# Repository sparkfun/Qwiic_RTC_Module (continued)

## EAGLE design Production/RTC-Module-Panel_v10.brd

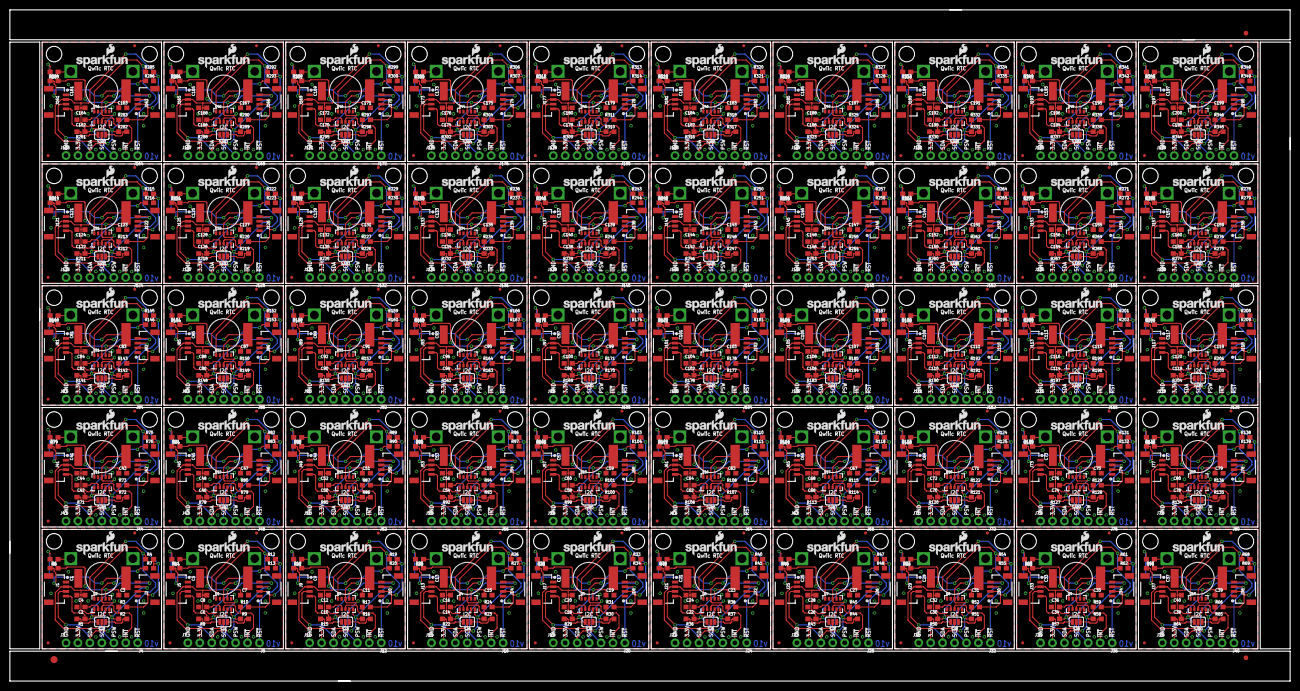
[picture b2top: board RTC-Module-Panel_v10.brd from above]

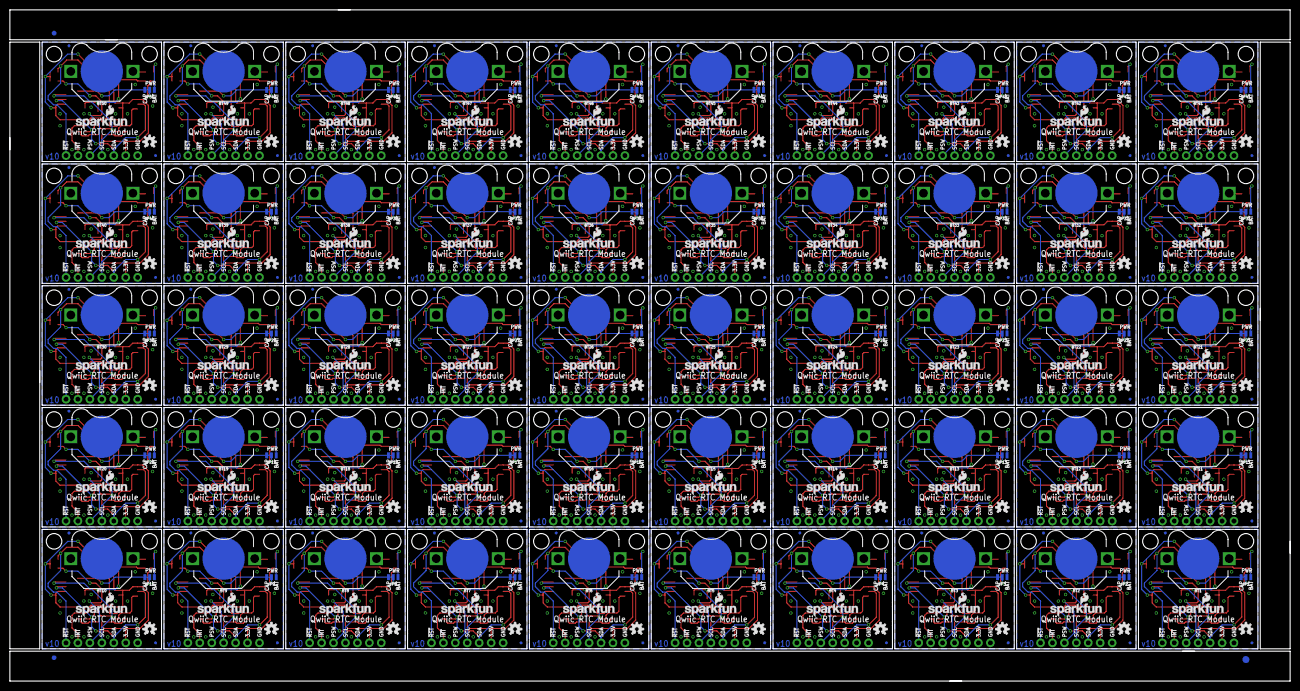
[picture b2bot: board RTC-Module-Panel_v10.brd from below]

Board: 2 copper layers, 272.3 x 142.7 mm, 1406 parts (303 on the bottom side), 750 nets.

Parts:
BT1, BT2, BT3, BT4, BT5, BT6, BT7, BT8, BT9, BT10, BT11, BT12, BT13, BT14, BT15, BT16, BT17, BT18, BT19, BT20, BT21, BT22, BT23, BT24, BT25, BT26, BT27, BT28, BT29, BT30, BT31, BT32, BT33, BT34, BT35, BT36, BT37, BT38, BT39, BT40, BT41, BT42, BT43, BT44, BT45, BT46, BT47, BT48, BT49, BT50: BATTCON_12MM_PTH
C1, C5, C9, C13, C17, C21, C25, C29, C33, C37, C41, C45, C49, C53, C57, C61, C65, C69, C73, C77, C81, C85, C89, C93, C97, C101, C105, C109, C113, C117, C121, C125, C129, C133, C137, C141, C145, C149, C153, C157, C161, C165, C169, C173, C177, C181, C185, C189, C193, C197: .22F-SUPERCAP; DSK-RADIAL-6.8MM
C2, C6, C10, C14, C18, C22, C26, C30, C34, C38, C42, C46, C50, C54, C58, C62, C66, C70, C74, C78, C82, C86, C90, C94, C98, C102, C106, C110, C114, C118, C122, C126, C130, C134, C138, C142, C146, C150, C154, C158, C162, C166, C170, C174, C178, C182, C186, C190, C194, C198: 47pF; 0603
C3, C4, C7, C8, C11, C12, C15, C16, C19, C20, C23, C24, C27, C28, C31, C32, C35, C36, C39, C40, C43, C44, C47, C48, C51, C52, C55, C56, C59, C60, C63, C64, C67, C68, C71, C72, C75, C76, C79, C80, C83, C84, C87, C88, C91, C92, C95, C96, C99, C100, C103, C104, C107, C108, C111, C112, C115, C116, C119, C120, C123, C124, C127, C128, C131, C132, C135, C136, C139, C140, C143, C144, C147, C148, C151, C152, C155, C156, C159, C160, C163, C164, C167, C168, C171, C172, C175, C176, C179, C180, C183, C184, C187, C188, C191, C192, C195, C196, C199, C200: 10nF; 0603
E$1, E$2: FIDUCIAL-1.5X3
E$3, E$4, E$6, E$7: FIDUCIAL-1X2
FD1, FD2, FD3, FD4, FD5, FD6, FD7, FD8, FD9, FD10, FD11, FD12, FD13, FD14, FD15, FD16, FD17, FD18, FD19, FD20, FD21, FD22, FD23, FD24, FD25, FD26, FD27, FD28, FD29, FD30, FD31, FD32, FD33, FD34, FD35, FD36, FD37, FD38, FD39, FD40, FD41, FD42, FD43, FD44, FD45, FD46, FD47, FD48, FD49, FD50, FD51, FD52, FD53, FD54, FD55, FD56, FD57, FD58, FD59, FD60, FD61, FD62, FD63, FD64, FD65, FD66, FD67, FD68, FD69, FD70, FD71, FD72, FD73, FD74, FD75, FD76, FD77, FD78, FD79, FD80, FD81, FD82, FD83, FD84, FD85, FD86, FD87, FD88, FD89, FD90, FD91, FD92, FD93, FD94, FD95, FD96, FD97, FD98, FD99, FD100, FD101, FD102, FD103, FD104, FD105, FD106, FD107, FD108, FD109, FD110, FD111, FD112, FD113, FD114, FD115, FD116, FD117, FD118, FD119, FD120, FD121, FD122, FD123, FD124, FD125, FD126, FD127, FD128, FD129, FD130, FD131, FD132, FD133, FD134, FD135, FD136, FD137, FD138, FD139, FD140, FD141, FD142, FD143, FD144, FD145, FD146, FD147, FD148, FD149, FD150, FD151, FD152, FD153, FD154, FD155, FD156, FD157, FD158, FD159, FD160, FD161, FD162, FD163, FD164, FD165, FD166, FD167, FD168, FD169, FD170, FD171, FD172, FD173, FD174, FD175, FD176, FD177, FD178, FD179, FD180, FD181, FD182, FD183, FD184, FD185, FD186, FD187, FD188, FD189, FD190, FD191, FD192, FD193, FD194, FD195, FD196, FD197, FD198, FD199, FD200: FIDUCIALUFIDUCIAL; FIDUCIAL-MICRO
J1, J2, J5, J6, J9, J10, J13, J14, J17, J18, J21, J22, J25, J26, J29, J30, J33, J34, J37, J38, J41, J42, J45, J46, J49, J50, J53, J54, J57, J58, J61, J62, J65, J66, J69, J70, J73, J74, J77, J78, J81, J82, J85, J86, J89, J90, J93, J94, J97, J98, J101, J102, J105, J106, J109, J110, J113, J114, J117, J118, J121, J122, J125, J126, J129, J130, J133, J134, J137, J138, J141, J142, J145, J146, J149, J150, J153, J154, J157, J158, J161, J162, J165, J166, J169, J170, J173, J174, J177, J178, J181, J182, J185, J186, J189, J190, J193, J194, J197, J198: SMD; 1X04_1MM_RA
J3, J7, J11, J15, J19, J23, J27, J31, J35, J39, J43, J47, J51, J55, J59, J63, J67, J71, J75, J79, J83, J87, J91, J95, J99, J103, J107, J111, J115, J119, J123, J127, J131, J135, J139, J143, J147, J151, J155, J159, J163, J167, J171, J175, J179, J183, J187, J191, J195, J199: PTH; 1X04_NO_SILK
J4, J8, J12, J16, J20, J24, J28, J32, J36, J40, J44, J48, J52, J56, J60, J64, J68, J72, J76, J80, J84, J88, J92, J96, J100, J104, J108, J112, J116, J120, J124, J128, J132, J136, J140, J144, J148, J152, J156, J160, J164, J168, J172, J176, J180, J184, J188, J192, J196, J200: 1X03_NO_SILK
JP1, JP2, JP3, JP4, JP5, JP6, JP7, JP8, JP9, JP10, JP11, JP12, JP13, JP14, JP15, JP16, JP17, JP18, JP19, JP20, JP21, JP22, JP23, JP24, JP25, JP26, JP27, JP28, JP29, JP30, JP31, JP32, JP33, JP34, JP35, JP36, JP37, JP38, JP39, JP40, JP41, JP42, JP43, JP44, JP45, JP46, JP47, JP48, JP49, JP50: JUMPER-SMT_3_1-NC_TRACE_NO-SILK; SMT-JUMPER_3_1-NC_TRACE_NO-SILK
LOGO1, LOGO4, LOGO7, LOGO10, LOGO13, LOGO16, LOGO19, LOGO22, LOGO25, LOGO28, LOGO31, LOGO34, LOGO37, LOGO40, LOGO43, LOGO46, LOGO49, LOGO52, LOGO55, LOGO58, LOGO61, LOGO64, LOGO67, LOGO70, LOGO73, LOGO76, LOGO79, LOGO82, LOGO85, LOGO88, LOGO91, LOGO94, LOGO97, LOGO100, LOGO103, LOGO106, LOGO109, LOGO112, LOGO115, LOGO118, LOGO121, LOGO124, LOGO127, LOGO130, LOGO133, LOGO136, LOGO139, LOGO142, LOGO145, LOGO148: OSHW-LOGOS; OSHW-LOGO-S
LOGO2, LOGO3, LOGO5, LOGO6, LOGO8, LOGO9, LOGO11, LOGO12, LOGO14, LOGO15, LOGO17, LOGO18, LOGO20, LOGO21, LOGO23, LOGO24, LOGO26, LOGO27, LOGO29, LOGO30, LOGO32, LOGO33, LOGO35, LOGO36, LOGO38, LOGO39, LOGO41, LOGO42, LOGO44, LOGO45, LOGO47, LOGO48, LOGO50, LOGO51, LOGO53, LOGO54, LOGO56, LOGO57, LOGO59, LOGO60, LOGO62, LOGO63, LOGO65, LOGO66, LOGO68, LOGO69, LOGO71, LOGO72, LOGO74, LOGO75, LOGO77, LOGO78, LOGO80, LOGO81, LOGO83, LOGO84, LOGO86, LOGO87, LOGO89, LOGO90, LOGO92, LOGO93, LOGO95, LOGO96, LOGO98, LOGO99, LOGO101, LOGO102, LOGO104, LOGO105, LOGO107, LOGO108, LOGO110, LOGO111, LOGO113, LOGO114, LOGO116, LOGO117, LOGO119, LOGO120, LOGO122, LOGO123, LOGO125, LOGO126, LOGO128, LOGO129, LOGO131, LOGO132, LOGO134, LOGO135, LOGO137, LOGO138, LOGO140, LOGO141, LOGO143, LOGO144, LOGO146, LOGO147, LOGO149, LOGO150: SFE_LOGO_NAME_FLAME.1_INCH; SFE_LOGO_NAME_FLAME_.1
R1, R2, R8, R9, R15, R16, R22, R23, R29, R30, R36, R37, R43, R44, R50, R51, R57, R58, R64, R65, R71, R72, R78, R79, R85, R86, R92, R93, R99, R100, R106, R107, R113, R114, R120, R121, R127, R128, R134, R135, R141, R142, R148, R149, R155, R156, R162, R163, R169, R170, R176, R177, R183, R184, R190, R191, R197, R198, R204, R205, R211, R212, R218, R219, R225, R226, R232, R233, R239, R240, R246, R247, R253, R254, R260, R261, R267, R268, R274, R275, R281, R282, R288, R289, R295, R296, R302, R303, R309, R310, R316, R317, R323, R324, R330, R331, R337, R338, R344, R345: 2.2k; 0603
R3, R4, R7, R10, R12, R13, R17, R19, R20, R24, R26, R27, R31, R33, R34, R38, R40, R41, R45, R47, R48, R52, R54, R55, R59, R61, R62, R66, R68, R69, R73, R75, R76, R80, R82, R83, R87, R89, R90, R94, R96, R97, R101, R103, R104, R108, R110, R111, R115, R117, R118, R122, R124, R125, R129, R131, R132, R136, R138, R139, R143, R145, R146, R150, R152, R153, R157, R159, R160, R164, R166, R167, R171, R173, R174, R178, R180, R181, R185, R187, R188, R192, R194, R195, R199, R201, R202, R206, R208, R209, R213, R215, R216, R220, R222, R223, R227, R229, R230, R234, R236, R237, R241, R243, R244, R248, R250, R251, R255, R257, R258, R262, R264, R265, R269, R271, R272, R276, R278, R279, R283, R285, R286, R290, R292, R293, R297, R299, R300, R304, R306, R307, R311, R313, R314, R318, R320, R321, R325, R327, R328, R332, R334, R335, R339, R341, R342, R346, R348, R349: 10k; 0603
R5, R14, R21, R28, R35, R42, R49, R56, R63, R70, R77, R84, R91, R98, R105, R112, R119, R126, R133, R140, R147, R154, R161, R168, R175, R182, R189, R196, R203, R210, R217, R224, R231, R238, R245, R252, R259, R266, R273, R280, R287, R294, R301, R308, R315, R322, R329, R336, R343, R350: 470; 0603
R6, R11, R18, R25, R32, R39, R46, R53, R60, R67, R74, R81, R88, R95, R102, R109, R116, R123, R130, R137, R144, R151, R158, R165, R172, R179, R186, R193, R200, R207, R214, R221, R228, R235, R242, R249, R256, R263, R270, R277, R284, R291, R298, R305, R312, R319, R326, R333, R340, R347: 1k; 0603
SJ1, SJ2, SJ3, SJ4, SJ5, SJ6, SJ7, SJ8, SJ9, SJ10, SJ11, SJ12, SJ13, SJ14, SJ15, SJ16, SJ17, SJ18, SJ19, SJ20, SJ21, SJ22, SJ23, SJ24, SJ25, SJ26, SJ27, SJ28, SJ29, SJ30, SJ31, SJ32, SJ33, SJ34, SJ35, SJ36, SJ37, SJ38, SJ39, SJ40, SJ41, SJ42, SJ43, SJ44, SJ45, SJ46, SJ47, SJ48, SJ49, SJ50: JUMPER-SMT_3_2-NC_PASTE_SILK; SMT-JUMPER_3_2-NC_PASTE_SILK
U1, U2, U3, U4, U5, U6, U7, U8, U9, U10, U11, U12, U13, U14, U15, U16, U17, U18, U19, U20, U21, U22, U23, U24, U25, U26, U27, U28, U29, U30, U31, U32, U33, U34, U35, U36, U37, U38, U39, U40, U41, U42, U43, U44, U45, U46, U47, U48, U49, U50: RV-1805
U$1, U$2, U$3, U$4, U$5, U$6, U$7, U$8, U$9, U$10, U$11, U$12, U$13, U$14, U$15, U$16, U$17, U$18, U$19, U$20, U$21, U$22, U$23, U$24, U$25, U$26, U$27, U$28, U$29, U$30, U$31, U$32, U$33, U$34, U$35, U$36, U$37, U$38, U$39, U$40, U$41, U$42, U$43, U$44, U$45, U$46, U$47, U$48, U$49, U$50, U$51, U$52, U$53, U$54, U$55, U$56, U$57, U$58, U$59, U$60, U$61, U$62, U$63, U$64, U$65, U$66, U$67, U$68, U$69, U$70, U$71, U$72, U$73, U$74, U$75, U$76, U$77, U$78, U$79, U$80, U$81, U$82, U$83, U$84, U$85, U$86, U$87, U$88, U$89, U$90, U$91, U$92, U$93, U$94, U$95, U$96, U$97, U$98, U$99, U$100: STAND-OFF

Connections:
3.3V: C4.1, J1.2, J2.2, J3.2, R3.2, R4.2, R7.2, SJ2.2, U2.1
3.3V1: C8.1, J5.2, J6.2, J7.2, R10.2, R12.2, R13.2, SJ1.2, U1.1
3.3V2: C12.1, J9.2, J10.2, J11.2, R17.2, R19.2, R20.2, SJ3.2, U3.1
3.3V3: C16.1, J13.2, J14.2, J15.2, R24.2, R26.2, R27.2, SJ4.2, U4.1
3.3V4: C20.1, J17.2, J18.2, J19.2, R31.2, R33.2, R34.2, SJ5.2, U5.1
3.3V5: C24.1, J21.2, J22.2, J23.2, R38.2, R40.2, R41.2, SJ6.2, U6.1
3.3V6: C28.1, J25.2, J26.2, J27.2, R45.2, R47.2, R48.2, SJ7.2, U7.1
3.3V7: C32.1, J29.2, J30.2, J31.2, R52.2, R54.2, R55.2, SJ8.2, U8.1
3.3V8: C36.1, J33.2, J34.2, J35.2, R59.2, R61.2, R62.2, SJ9.2, U9.1
3.3V9: C40.1, J37.2, J38.2, J39.2, R66.2, R68.2, R69.2, SJ10.2, U10.1
3.3V10: C44.1, J41.2, J42.2, J43.2, R73.2, R75.2, R76.2, SJ11.2, U11.1
3.3V11: C48.1, J45.2, J46.2, J47.2, R80.2, R82.2, R83.2, SJ12.2, U12.1
3.3V12: C52.1, J49.2, J50.2, J51.2, R87.2, R89.2, R90.2, SJ13.2, U13.1
3.3V13: C56.1, J53.2, J54.2, J55.2, R94.2, R96.2, R97.2, SJ14.2, U14.1
3.3V14: C60.1, J57.2, J58.2, J59.2, R101.2, R103.2, R104.2, SJ15.2, U15.1
3.3V15: C64.1, J61.2, J62.2, J63.2, R108.2, R110.2, R111.2, SJ16.2, U16.1
3.3V16: C68.1, J65.2, J66.2, J67.2, R115.2, R117.2, R118.2, SJ17.2, U17.1
3.3V17: C72.1, J69.2, J70.2, J71.2, R122.2, R124.2, R125.2, SJ18.2, U18.1
3.3V18: C76.1, J73.2, J74.2, J75.2, R129.2, R131.2, R132.2, SJ19.2, U19.1
3.3V19: C80.1, J77.2, J78.2, J79.2, R136.2, R138.2, R139.2, SJ20.2, U20.1
3.3V20: C84.1, J81.2, J82.2, J83.2, R143.2, R145.2, R146.2, SJ21.2, U21.1
3.3V21: C88.1, J85.2, J86.2, J87.2, R150.2, R152.2, R153.2, SJ22.2, U22.1
3.3V22: C92.1, J89.2, J90.2, J91.2, R157.2, R159.2, R160.2, SJ23.2, U23.1
3.3V23: C96.1, J93.2, J94.2, J95.2, R164.2, R166.2, R167.2, SJ24.2, U24.1
3.3V24: C100.1, J97.2, J98.2, J99.2, R171.2, R173.2, R174.2, SJ25.2, U25.1
3.3V25: C104.1, J101.2, J102.2, J103.2, R178.2, R180.2, R181.2, SJ26.2, U26.1
3.3V26: C108.1, J105.2, J106.2, J107.2, R185.2, R187.2, R188.2, SJ27.2, U27.1
3.3V27: C112.1, J109.2, J110.2, J111.2, R192.2, R194.2, R195.2, SJ28.2, U28.1
3.3V28: C116.1, J113.2, J114.2, J115.2, R199.2, R201.2, R202.2, SJ29.2, U29.1
3.3V29: C120.1, J117.2, J118.2, J119.2, R206.2, R208.2, R209.2, SJ30.2, U30.1
3.3V30: C124.1, J121.2, J122.2, J123.2, R213.2, R215.2, R216.2, SJ31.2, U31.1
3.3V31: C128.1, J125.2, J126.2, J127.2, R220.2, R222.2, R223.2, SJ32.2, U32.1
3.3V32: C132.1, J129.2, J130.2, J131.2, R227.2, R229.2, R230.2, SJ33.2, U33.1
3.3V33: C136.1, J133.2, J134.2, J135.2, R234.2, R236.2, R237.2, SJ34.2, U34.1
3.3V34: C140.1, J137.2, J138.2, J139.2, R241.2, R243.2, R244.2, SJ35.2, U35.1
3.3V35: C144.1, J141.2, J142.2, J143.2, R248.2, R250.2, R251.2, SJ36.2, U36.1
3.3V36: C148.1, J145.2, J146.2, J147.2, R255.2, R257.2, R258.2, SJ37.2, U37.1
3.3V37: C152.1, J149.2, J150.2, J151.2, R262.2, R264.2, R265.2, SJ38.2, U38.1
3.3V38: C156.1, J153.2, J154.2, J155.2, R269.2, R271.2, R272.2, SJ39.2, U39.1
3.3V39: C160.1, J157.2, J158.2, J159.2, R276.2, R278.2, R279.2, SJ40.2, U40.1
3.3V40: C164.1, J161.2, J162.2, J163.2, R283.2, R285.2, R286.2, SJ41.2, U41.1
3.3V41: C168.1, J165.2, J166.2, J167.2, R290.2, R292.2, R293.2, SJ42.2, U42.1
3.3V42: C172.1, J169.2, J170.2, J171.2, R297.2, R299.2, R300.2, SJ43.2, U43.1
3.3V43: C176.1, J173.2, J174.2, J175.2, R304.2, R306.2, R307.2, SJ44.2, U44.1
3.3V44: C180.1, J177.2, J178.2, J179.2, R311.2, R313.2, R314.2, SJ45.2, U45.1
3.3V45: C184.1, J181.2, J182.2, J183.2, R318.2, R320.2, R321.2, SJ46.2, U46.1
3.3V46: C188.1, J185.2, J186.2, J187.2, R325.2, R327.2, R328.2, SJ47.2, U47.1
3.3V47: C192.1, J189.2, J190.2, J191.2, R332.2, R334.2, R335.2, SJ48.2, U48.1
3.3V48: C196.1, J193.2, J194.2, J195.2, R339.2, R341.2, R342.2, SJ49.2, U49.1
3.3V49: C200.1, J197.2, J198.2, J199.2, R346.2, R348.2, R349.2, SJ50.2, U50.1
!INT: J4.2, R3.1, U2.3
!INT1: J8.2, R10.1, U1.3
!INT2: J12.2, R17.1, U3.3
!INT3: J16.2, R24.1, U4.3
!INT4: J20.2, R31.1, U5.3
!INT5: J24.2, R38.1, U6.3
!INT6: J28.2, R45.1, U7.3
!INT7: J32.2, R52.1, U8.3
!INT8: J36.2, R59.1, U9.3
!INT9: J40.2, R66.1, U10.3
!INT10: J44.2, R73.1, U11.3
!INT11: J48.2, R80.1, U12.3
!INT12: J52.2, R87.1, U13.3
!INT13: J56.2, R94.1, U14.3
!INT14: J60.2, R101.1, U15.3
!INT15: J64.2, R108.1, U16.3
!INT16: J68.2, R115.1, U17.3
!INT17: J72.2, R122.1, U18.3
!INT18: J76.2, R129.1, U19.3
!INT19: J80.2, R136.1, U20.3
!INT20: J84.2, R143.1, U21.3
!INT21: J88.2, R150.1, U22.3
!INT22: J92.2, R157.1, U23.3
!INT23: J96.2, R164.1, U24.3
!INT24: J100.2, R171.1, U25.3
!INT25: J104.2, R178.1, U26.3
!INT26: J108.2, R185.1, U27.3
!INT27: J112.2, R192.1, U28.3
!INT28: J116.2, R199.1, U29.3
!INT29: J120.2, R206.1, U30.3
!INT30: J124.2, R213.1, U31.3
!INT31: J128.2, R220.1, U32.3
!INT32: J132.2, R227.1, U33.3
!INT33: J136.2, R234.1, U34.3
!INT34: J140.2, R241.1, U35.3
!INT35: J144.2, R248.1, U36.3
!INT36: J148.2, R255.1, U37.3
!INT37: J152.2, R262.1, U38.3
!INT38: J156.2, R269.1, U39.3
!INT39: J160.2, R276.1, U40.3
!INT40: J164.2, R283.1, U41.3
!INT41: J168.2, R290.1, U42.3
!INT42: J172.2, R297.1, U43.3
!INT43: J176.2, R304.1, U44.3
!INT44: J180.2, R311.1, U45.3
!INT45: J184.2, R318.1, U46.3
!INT46: J188.2, R325.1, U47.3
!INT47: J192.2, R332.1, U48.3
!INT48: J196.2, R339.1, U49.3
!INT49: J200.2, R346.1, U50.3
!RST: J4.1, R4.1, U2.10
!RST1: J8.1, R12.1, U1.10
!RST2: J12.1, R19.1, U3.10
!RST3: J16.1, R26.1, U4.10
!RST4: J20.1, R33.1, U5.10
!RST5: J24.1, R40.1, U6.10
!RST6: J28.1, R47.1, U7.10
!RST7: J32.1, R54.1, U8.10
!RST8: J36.1, R61.1, U9.10
!RST9: J40.1, R68.1, U10.10
!RST10: J44.1, R75.1, U11.10
!RST11: J48.1, R82.1, U12.10
!RST12: J52.1, R89.1, U13.10
!RST13: J56.1, R96.1, U14.10
!RST14: J60.1, R103.1, U15.10
!RST15: J64.1, R110.1, U16.10
!RST16: J68.1, R117.1, U17.10
!RST17: J72.1, R124.1, U18.10
!RST18: J76.1, R131.1, U19.10
!RST19: J80.1, R138.1, U20.10
!RST20: J84.1, R145.1, U21.10
!RST21: J88.1, R152.1, U22.10
!RST22: J92.1, R159.1, U23.10
!RST23: J96.1, R166.1, U24.10
!RST24: J100.1, R173.1, U25.10
!RST25: J104.1, R180.1, U26.10
!RST26: J108.1, R187.1, U27.10
!RST27: J112.1, R194.1, U28.10
!RST28: J116.1, R201.1, U29.10
!RST29: J120.1, R208.1, U30.10
!RST30: J124.1, R215.1, U31.10
!RST31: J128.1, R222.1, U32.10
!RST32: J132.1, R229.1, U33.10
!RST33: J136.1, R236.1, U34.10
!RST34: J140.1, R243.1, U35.10
!RST35: J144.1, R250.1, U36.10
!RST36: J148.1, R257.1, U37.10
!RST37: J152.1, R264.1, U38.10
!RST38: J156.1, R271.1, U39.10
!RST39: J160.1, R278.1, U40.10
!RST40: J164.1, R285.1, U41.10
!RST41: J168.1, R292.1, U42.10
!RST42: J172.1, R299.1, U43.10
!RST43: J176.1, R306.1, U44.10
!RST44: J180.1, R313.1, U45.10
!RST45: J184.1, R320.1, U46.10
!RST46: J188.1, R327.1, U47.10
!RST47: J192.1, R334.1, U48.10
!RST48: J196.1, R341.1, U49.10
!RST49: J200.1, R348.1, U50.10
GND: BT1.GND, C1.-, C2.2, C3.2, C4.2, J1.1, J2.1, J3.1, U2.6, U2.9
GND1: BT2.GND, C5.-, C6.2, C7.2, C8.2, J5.1, J6.1, J7.1, U1.6, U1.9
GND2: BT3.GND, C9.-, C10.2, C11.2, C12.2, J9.1, J10.1, J11.1, U3.6, U3.9
GND3: BT4.GND, C13.-, C14.2, C15.2, C16.2, J13.1, J14.1, J15.1, U4.6, U4.9
GND4: BT5.GND, C17.-, C18.2, C19.2, C20.2, J17.1, J18.1, J19.1, U5.6, U5.9
GND5: BT6.GND, C21.-, C22.2, C23.2, C24.2, J21.1, J22.1, J23.1, U6.6, U6.9
GND6: BT7.GND, C25.-, C26.2, C27.2, C28.2, J25.1, J26.1, J27.1, U7.6, U7.9
GND7: BT8.GND, C29.-, C30.2, C31.2, C32.2, J29.1, J30.1, J31.1, U8.6, U8.9
GND8: BT9.GND, C33.-, C34.2, C35.2, C36.2, J33.1, J34.1, J35.1, U9.6, U9.9
GND9: BT10.GND, C37.-, C38.2, C39.2, C40.2, J37.1, J38.1, J39.1, U10.6, U10.9
GND10: BT11.GND, C41.-, C42.2, C43.2, C44.2, J41.1, J42.1, J43.1, U11.6, U11.9
GND11: BT12.GND, C45.-, C46.2, C47.2, C48.2, J45.1, J46.1, J47.1, U12.6, U12.9
GND12: BT13.GND, C49.-, C50.2, C51.2, C52.2, J49.1, J50.1, J51.1, U13.6, U13.9
GND13: BT14.GND, C53.-, C54.2, C55.2, C56.2, J53.1, J54.1, J55.1, U14.6, U14.9
GND14: BT15.GND, C57.-, C58.2, C59.2, C60.2, J57.1, J58.1, J59.1, U15.6, U15.9
GND15: BT16.GND, C61.-, C62.2, C63.2, C64.2, J61.1, J62.1, J63.1, U16.6, U16.9
GND16: BT17.GND, C65.-, C66.2, C67.2, C68.2, J65.1, J66.1, J67.1, U17.6, U17.9
GND17: BT18.GND, C69.-, C70.2, C71.2, C72.2, J69.1, J70.1, J71.1, U18.6, U18.9
GND18: BT19.GND, C73.-, C74.2, C75.2, C76.2, J73.1, J74.1, J75.1, U19.6, U19.9
GND19: BT20.GND, C77.-, C78.2, C79.2, C80.2, J77.1, J78.1, J79.1, U20.6, U20.9
GND20: BT21.GND, C81.-, C82.2, C83.2, C84.2, J81.1, J82.1, J83.1, U21.6, U21.9
GND21: BT22.GND, C85.-, C86.2, C87.2, C88.2, J85.1, J86.1, J87.1, U22.6, U22.9
GND22: BT23.GND, C89.-, C90.2, C91.2, C92.2, J89.1, J90.1, J91.1, U23.6, U23.9
GND23: BT24.GND, C93.-, C94.2, C95.2, C96.2, J93.1, J94.1, J95.1, U24.6, U24.9
GND24: BT25.GND, C97.-, C98.2, C99.2, C100.2, J97.1, J98.1, J99.1, U25.6, U25.9
GND25: BT26.GND, C101.-, C102.2, C103.2, C104.2, J101.1, J102.1, J103.1, U26.6, U26.9
GND26: BT27.GND, C105.-, C106.2, C107.2, C108.2, J105.1, J106.1, J107.1, U27.6, U27.9
GND27: BT28.GND, C109.-, C110.2, C111.2, C112.2, J109.1, J110.1, J111.1, U28.6, U28.9
GND28: BT29.GND, C113.-, C114.2, C115.2, C116.2, J113.1, J114.1, J115.1, U29.6, U29.9
GND29: BT30.GND, C117.-, C118.2, C119.2, C120.2, J117.1, J118.1, J119.1, U30.6, U30.9
GND30: BT31.GND, C121.-, C122.2, C123.2, C124.2, J121.1, J122.1, J123.1, U31.6, U31.9
GND31: BT32.GND, C125.-, C126.2, C127.2, C128.2, J125.1, J126.1, J127.1, U32.6, U32.9
GND32: BT33.GND, C129.-, C130.2, C131.2, C132.2, J129.1, J130.1, J131.1, U33.6, U33.9
GND33: BT34.GND, C133.-, C134.2, C135.2, C136.2, J133.1, J134.1, J135.1, U34.6, U34.9
GND34: BT35.GND, C137.-, C138.2, C139.2, C140.2, J137.1, J138.1, J139.1, U35.6, U35.9
GND35: BT36.GND, C141.-, C142.2, C143.2, C144.2, J141.1, J142.1, J143.1, U36.6, U36.9
GND36: BT37.GND, C145.-, C146.2, C147.2, C148.2, J145.1, J146.1, J147.1, U37.6, U37.9
GND37: BT38.GND, C149.-, C150.2, C151.2, C152.2, J149.1, J150.1, J151.1, U38.6, U38.9
GND38: BT39.GND, C153.-, C154.2, C155.2, C156.2, J153.1, J154.1, J155.1, U39.6, U39.9
GND39: BT40.GND, C157.-, C158.2, C159.2, C160.2, J157.1, J158.1, J159.1, U40.6, U40.9
GND40: BT41.GND, C161.-, C162.2, C163.2, C164.2, J161.1, J162.1, J163.1, U41.6, U41.9
GND41: BT42.GND, C165.-, C166.2, C167.2, C168.2, J165.1, J166.1, J167.1, U42.6, U42.9
GND42: BT43.GND, C169.-, C170.2, C171.2, C172.2, J169.1, J170.1, J171.1, U43.6, U43.9
GND43: BT44.GND, C173.-, C174.2, C175.2, C176.2, J173.1, J174.1, J175.1, U44.6, U44.9
GND44: BT45.GND, C177.-, C178.2, C179.2, C180.2, J177.1, J178.1, J179.1, U45.6, U45.9
GND45: BT46.GND, C181.-, C182.2, C183.2, C184.2, J181.1, J182.1, J183.1, U46.6, U46.9
GND46: BT47.GND, C185.-, C186.2, C187.2, C188.2, J185.1, J186.1, J187.1, U47.6, U47.9
GND47: BT48.GND, C189.-, C190.2, C191.2, C192.2, J189.1, J190.1, J191.1, U48.6, U48.9
GND48: BT49.GND, C193.-, C194.2, C195.2, C196.2, J193.1, J194.1, J195.1, U49.6, U49.9
GND49: BT50.GND, C197.-, C198.2, C199.2, C200.2, J197.1, J198.1, J199.1, U50.6, U50.9
unnamed: R1.2, SJ2.3
unnamed: R2.2, SJ2.1
unnamed: BT1.VCC@1, R5.1
unnamed: C2.1, U2.2
unnamed: JP1.2, R6.1
unnamed: C1.+, JP1.3
unnamed: JP1.1, R5.2
unnamed: R8.2, SJ1.3
unnamed: R9.2, SJ1.1
unnamed: C6.1, U1.2
unnamed: BT2.VCC@1, R14.1
unnamed: JP2.2, R11.1
unnamed: C5.+, JP2.3
unnamed: JP2.1, R14.2
unnamed: R15.2, SJ3.3
unnamed: R16.2, SJ3.1
unnamed: C10.1, U3.2
unnamed: BT3.VCC@1, R21.1
unnamed: JP3.2, R18.1
unnamed: C9.+, JP3.3
unnamed: JP3.1, R21.2
unnamed: R22.2, SJ4.3
unnamed: R23.2, SJ4.1
unnamed: C14.1, U4.2
unnamed: BT4.VCC@1, R28.1
unnamed: JP4.2, R25.1
unnamed: C13.+, JP4.3
unnamed: JP4.1, R28.2
unnamed: R29.2, SJ5.3
unnamed: R30.2, SJ5.1
unnamed: C18.1, U5.2
unnamed: BT5.VCC@1, R35.1
unnamed: JP5.2, R32.1
unnamed: C17.+, JP5.3
unnamed: JP5.1, R35.2
unnamed: R36.2, SJ6.3
unnamed: R37.2, SJ6.1
unnamed: C22.1, U6.2
unnamed: BT6.VCC@1, R42.1
unnamed: JP6.2, R39.1
unnamed: C21.+, JP6.3
unnamed: JP6.1, R42.2
unnamed: R43.2, SJ7.3
unnamed: R44.2, SJ7.1
unnamed: C26.1, U7.2
unnamed: BT7.VCC@1, R49.1
unnamed: JP7.2, R46.1
unnamed: C25.+, JP7.3
unnamed: JP7.1, R49.2
unnamed: R50.2, SJ8.3
unnamed: R51.2, SJ8.1
unnamed: C30.1, U8.2
unnamed: BT8.VCC@1, R56.1
unnamed: JP8.2, R53.1
unnamed: C29.+, JP8.3
unnamed: JP8.1, R56.2
unnamed: R57.2, SJ9.3
unnamed: R58.2, SJ9.1
unnamed: C34.1, U9.2
unnamed: BT9.VCC@1, R63.1
unnamed: JP9.2, R60.1
unnamed: C33.+, JP9.3
unnamed: JP9.1, R63.2
unnamed: R64.2, SJ10.3
unnamed: R65.2, SJ10.1
unnamed: C38.1, U10.2
unnamed: BT10.VCC@1, R70.1
unnamed: JP10.2, R67.1
unnamed: C37.+, JP10.3
unnamed: JP10.1, R70.2
unnamed: R71.2, SJ11.3
unnamed: R72.2, SJ11.1
unnamed: C42.1, U11.2
unnamed: BT11.VCC@1, R77.1
unnamed: JP11.2, R74.1
unnamed: C41.+, JP11.3
unnamed: JP11.1, R77.2
unnamed: R78.2, SJ12.3
unnamed: R79.2, SJ12.1
unnamed: C46.1, U12.2
unnamed: BT12.VCC@1, R84.1
unnamed: JP12.2, R81.1
unnamed: C45.+, JP12.3
unnamed: JP12.1, R84.2
unnamed: R85.2, SJ13.3
unnamed: R86.2, SJ13.1
unnamed: C50.1, U13.2
unnamed: BT13.VCC@1, R91.1
unnamed: JP13.2, R88.1
unnamed: C49.+, JP13.3
unnamed: JP13.1, R91.2
unnamed: R92.2, SJ14.3
unnamed: R93.2, SJ14.1
unnamed: C54.1, U14.2
unnamed: BT14.VCC@1, R98.1
unnamed: JP14.2, R95.1
unnamed: C53.+, JP14.3
unnamed: JP14.1, R98.2
unnamed: R99.2, SJ15.3
unnamed: R100.2, SJ15.1
unnamed: C58.1, U15.2
unnamed: BT15.VCC@1, R105.1
unnamed: JP15.2, R102.1
unnamed: C57.+, JP15.3
unnamed: JP15.1, R105.2
unnamed: R106.2, SJ16.3
unnamed: R107.2, SJ16.1
unnamed: C62.1, U16.2
unnamed: BT16.VCC@1, R112.1
unnamed: JP16.2, R109.1
unnamed: C61.+, JP16.3
unnamed: JP16.1, R112.2
unnamed: R113.2, SJ17.3
unnamed: R114.2, SJ17.1
unnamed: C66.1, U17.2
unnamed: BT17.VCC@1, R119.1
unnamed: JP17.2, R116.1
unnamed: C65.+, JP17.3
unnamed: JP17.1, R119.2
unnamed: R120.2, SJ18.3
unnamed: R121.2, SJ18.1
unnamed: C70.1, U18.2
unnamed: BT18.VCC@1, R126.1
unnamed: JP18.2, R123.1
unnamed: C69.+, JP18.3
unnamed: JP18.1, R126.2
unnamed: R127.2, SJ19.3
unnamed: R128.2, SJ19.1
unnamed: C74.1, U19.2
unnamed: BT19.VCC@1, R133.1
unnamed: JP19.2, R130.1
unnamed: C73.+, JP19.3
unnamed: JP19.1, R133.2
unnamed: R134.2, SJ20.3
unnamed: R135.2, SJ20.1
unnamed: C78.1, U20.2
unnamed: BT20.VCC@1, R140.1
unnamed: JP20.2, R137.1
unnamed: C77.+, JP20.3
unnamed: JP20.1, R140.2
unnamed: R141.2, SJ21.3
unnamed: R142.2, SJ21.1
unnamed: C82.1, U21.2
unnamed: BT21.VCC@1, R147.1
unnamed: JP21.2, R144.1
unnamed: C81.+, JP21.3
unnamed: JP21.1, R147.2
unnamed: R148.2, SJ22.3
unnamed: R149.2, SJ22.1
unnamed: C86.1, U22.2
unnamed: BT22.VCC@1, R154.1
unnamed: JP22.2, R151.1
unnamed: C85.+, JP22.3
unnamed: JP22.1, R154.2
unnamed: R155.2, SJ23.3
unnamed: R156.2, SJ23.1
unnamed: C90.1, U23.2
unnamed: BT23.VCC@1, R161.1
unnamed: JP23.2, R158.1
unnamed: C89.+, JP23.3
unnamed: JP23.1, R161.2
unnamed: R162.2, SJ24.3
unnamed: R163.2, SJ24.1
unnamed: C94.1, U24.2
unnamed: BT24.VCC@1, R168.1
unnamed: JP24.2, R165.1
unnamed: C93.+, JP24.3
unnamed: JP24.1, R168.2
unnamed: R169.2, SJ25.3
unnamed: R170.2, SJ25.1
unnamed: C98.1, U25.2
unnamed: BT25.VCC@1, R175.1
unnamed: JP25.2, R172.1
unnamed: C97.+, JP25.3
unnamed: JP25.1, R175.2
unnamed: R176.2, SJ26.3
unnamed: R177.2, SJ26.1
unnamed: C102.1, U26.2
unnamed: BT26.VCC@1, R182.1
unnamed: JP26.2, R179.1
unnamed: C101.+, JP26.3
unnamed: JP26.1, R182.2
unnamed: R183.2, SJ27.3
unnamed: R184.2, SJ27.1
unnamed: C106.1, U27.2
unnamed: BT27.VCC@1, R189.1
unnamed: JP27.2, R186.1
unnamed: C105.+, JP27.3
unnamed: JP27.1, R189.2
unnamed: R190.2, SJ28.3
unnamed: R191.2, SJ28.1
unnamed: C110.1, U28.2
unnamed: BT28.VCC@1, R196.1
unnamed: JP28.2, R193.1
unnamed: C109.+, JP28.3
unnamed: JP28.1, R196.2
unnamed: R197.2, SJ29.3
unnamed: R198.2, SJ29.1
unnamed: C114.1, U29.2
unnamed: BT29.VCC@1, R203.1
unnamed: JP29.2, R200.1
unnamed: C113.+, JP29.3
unnamed: JP29.1, R203.2
unnamed: R204.2, SJ30.3
unnamed: R205.2, SJ30.1
unnamed: C118.1, U30.2
unnamed: BT30.VCC@1, R210.1
unnamed: JP30.2, R207.1
unnamed: C117.+, JP30.3
unnamed: JP30.1, R210.2
unnamed: R211.2, SJ31.3
unnamed: R212.2, SJ31.1
unnamed: C122.1, U31.2
unnamed: BT31.VCC@1, R217.1
unnamed: JP31.2, R214.1
unnamed: C121.+, JP31.3
unnamed: JP31.1, R217.2
unnamed: R218.2, SJ32.3
unnamed: R219.2, SJ32.1
unnamed: C126.1, U32.2
unnamed: BT32.VCC@1, R224.1
unnamed: JP32.2, R221.1
unnamed: C125.+, JP32.3
unnamed: JP32.1, R224.2
unnamed: R225.2, SJ33.3
unnamed: R226.2, SJ33.1
unnamed: C130.1, U33.2
unnamed: BT33.VCC@1, R231.1
unnamed: JP33.2, R228.1
unnamed: C129.+, JP33.3
unnamed: JP33.1, R231.2
unnamed: R232.2, SJ34.3
unnamed: R233.2, SJ34.1
unnamed: C134.1, U34.2
unnamed: BT34.VCC@1, R238.1
unnamed: JP34.2, R235.1
unnamed: C133.+, JP34.3
unnamed: JP34.1, R238.2
unnamed: R239.2, SJ35.3
unnamed: R240.2, SJ35.1
unnamed: C138.1, U35.2
unnamed: BT35.VCC@1, R245.1
unnamed: JP35.2, R242.1
unnamed: C137.+, JP35.3
unnamed: JP35.1, R245.2
unnamed: R246.2, SJ36.3
unnamed: R247.2, SJ36.1
unnamed: C142.1, U36.2
unnamed: BT36.VCC@1, R252.1
unnamed: JP36.2, R249.1
unnamed: C141.+, JP36.3
unnamed: JP36.1, R252.2
unnamed: R253.2, SJ37.3
unnamed: R254.2, SJ37.1
unnamed: C146.1, U37.2
unnamed: BT37.VCC@1, R259.1
unnamed: JP37.2, R256.1
unnamed: C145.+, JP37.3
unnamed: JP37.1, R259.2
unnamed: R260.2, SJ38.3
unnamed: R261.2, SJ38.1
unnamed: C150.1, U38.2
unnamed: BT38.VCC@1, R266.1
unnamed: JP38.2, R263.1
unnamed: C149.+, JP38.3
unnamed: JP38.1, R266.2
unnamed: R267.2, SJ39.3
unnamed: R268.2, SJ39.1
unnamed: C154.1, U39.2
unnamed: BT39.VCC@1, R273.1
unnamed: JP39.2, R270.1
unnamed: C153.+, JP39.3
unnamed: JP39.1, R273.2
unnamed: R274.2, SJ40.3
unnamed: R275.2, SJ40.1
unnamed: C158.1, U40.2
unnamed: BT40.VCC@1, R280.1
unnamed: JP40.2, R277.1
unnamed: C157.+, JP40.3
unnamed: JP40.1, R280.2
unnamed: R281.2, SJ41.3
unnamed: R282.2, SJ41.1
unnamed: C162.1, U41.2
unnamed: BT41.VCC@1, R287.1
unnamed: JP41.2, R284.1
unnamed: C161.+, JP41.3
unnamed: JP41.1, R287.2
unnamed: R288.2, SJ42.3
unnamed: R289.2, SJ42.1
unnamed: C166.1, U42.2
unnamed: BT42.VCC@1, R294.1
unnamed: JP42.2, R291.1
unnamed: C165.+, JP42.3
unnamed: JP42.1, R294.2
unnamed: R295.2, SJ43.3
unnamed: R296.2, SJ43.1
unnamed: C170.1, U43.2
unnamed: BT43.VCC@1, R301.1
unnamed: JP43.2, R298.1
unnamed: C169.+, JP43.3
unnamed: JP43.1, R301.2
unnamed: R302.2, SJ44.3
unnamed: R303.2, SJ44.1
unnamed: C174.1, U44.2
unnamed: BT44.VCC@1, R308.1
unnamed: JP44.2, R305.1
unnamed: C173.+, JP44.3
unnamed: JP44.1, R308.2
unnamed: R309.2, SJ45.3
unnamed: R310.2, SJ45.1
unnamed: C178.1, U45.2
unnamed: BT45.VCC@1, R315.1
unnamed: JP45.2, R312.1
unnamed: C177.+, JP45.3
unnamed: JP45.1, R315.2
unnamed: R316.2, SJ46.3
unnamed: R317.2, SJ46.1
unnamed: C182.1, U46.2
unnamed: BT46.VCC@1, R322.1
unnamed: JP46.2, R319.1
unnamed: C181.+, JP46.3
unnamed: JP46.1, R322.2
unnamed: R323.2, SJ47.3
unnamed: R324.2, SJ47.1
unnamed: C186.1, U47.2
unnamed: BT47.VCC@1, R329.1
unnamed: JP47.2, R326.1
unnamed: C185.+, JP47.3
unnamed: JP47.1, R329.2
unnamed: R330.2, SJ48.3
unnamed: R331.2, SJ48.1
unnamed: C190.1, U48.2
unnamed: BT48.VCC@1, R336.1
unnamed: JP48.2, R333.1
unnamed: C189.+, JP48.3
unnamed: JP48.1, R336.2
unnamed: R337.2, SJ49.3
unnamed: R338.2, SJ49.1
unnamed: C194.1, U49.2
unnamed: BT49.VCC@1, R343.1
unnamed: JP49.2, R340.1
unnamed: C193.+, JP49.3
unnamed: JP49.1, R343.2
unnamed: R344.2, SJ50.3
unnamed: R345.2, SJ50.1
unnamed: C198.1, U50.2
unnamed: BT50.VCC@1, R350.1
unnamed: JP50.2, R347.1
unnamed: C197.+, JP50.3
unnamed: JP50.1, R350.2
PSW: J4.3, R7.1, U2.8
PSW1: J8.3, R13.1, U1.8
PSW2: J12.3, R20.1, U3.8
PSW3: J16.3, R27.1, U4.8
PSW4: J20.3, R34.1, U5.8
PSW5: J24.3, R41.1, U6.8
PSW6: J28.3, R48.1, U7.8
PSW7: J32.3, R55.1, U8.8
PSW8: J36.3, R62.1, U9.8
PSW9: J40.3, R69.1, U10.8
PSW10: J44.3, R76.1, U11.8
PSW11: J48.3, R83.1, U12.8
PSW12: J52.3, R90.1, U13.8
PSW13: J56.3, R97.1, U14.8
PSW14: J60.3, R104.1, U15.8
PSW15: J64.3, R111.1, U16.8
PSW16: J68.3, R118.1, U17.8
PSW17: J72.3, R125.1, U18.8
PSW18: J76.3, R132.1, U19.8
PSW19: J80.3, R139.1, U20.8
PSW20: J84.3, R146.1, U21.8
PSW21: J88.3, R153.1, U22.8
PSW22: J92.3, R160.1, U23.8
PSW23: J96.3, R167.1, U24.8
PSW24: J100.3, R174.1, U25.8
PSW25: J104.3, R181.1, U26.8
PSW26: J108.3, R188.1, U27.8
PSW27: J112.3, R195.1, U28.8
PSW28: J116.3, R202.1, U29.8
PSW29: J120.3, R209.1, U30.8
PSW30: J124.3, R216.1, U31.8
PSW31: J128.3, R223.1, U32.8
PSW32: J132.3, R230.1, U33.8
PSW33: J136.3, R237.1, U34.8
PSW34: J140.3, R244.1, U35.8
PSW35: J144.3, R251.1, U36.8
PSW36: J148.3, R258.1, U37.8
PSW37: J152.3, R265.1, U38.8
PSW38: J156.3, R272.1, U39.8
PSW39: J160.3, R279.1, U40.8
PSW40: J164.3, R286.1, U41.8
PSW41: J168.3, R293.1, U42.8
PSW42: J172.3, R300.1, U43.8
PSW43: J176.3, R307.1, U44.8
PSW44: J180.3, R314.1, U45.8
PSW45: J184.3, R321.1, U46.8
PSW46: J188.3, R328.1, U47.8
PSW47: J192.3, R335.1, U48.8
PSW48: J196.3, R342.1, U49.8
PSW49: J200.3, R349.1, U50.8
SCL: J1.4, J2.4, J3.4, R1.1, U2.4
SCL1: J5.4, J6.4, J7.4, R8.1, U1.4
SCL2: J9.4, J10.4, J11.4, R15.1, U3.4
SCL3: J13.4, J14.4, J15.4, R22.1, U4.4
SCL4: J17.4, J18.4, J19.4, R29.1, U5.4
SCL5: J21.4, J22.4, J23.4, R36.1, U6.4
SCL6: J25.4, J26.4, J27.4, R43.1, U7.4
SCL7: J29.4, J30.4, J31.4, R50.1, U8.4
SCL8: J33.4, J34.4, J35.4, R57.1, U9.4
SCL9: J37.4, J38.4, J39.4, R64.1, U10.4
SCL10: J41.4, J42.4, J43.4, R71.1, U11.4
SCL11: J45.4, J46.4, J47.4, R78.1, U12.4
SCL12: J49.4, J50.4, J51.4, R85.1, U13.4
SCL13: J53.4, J54.4, J55.4, R92.1, U14.4
SCL14: J57.4, J58.4, J59.4, R99.1, U15.4
SCL15: J61.4, J62.4, J63.4, R106.1, U16.4
SCL16: J65.4, J66.4, J67.4, R113.1, U17.4
SCL17: J69.4, J70.4, J71.4, R120.1, U18.4
SCL18: J73.4, J74.4, J75.4, R127.1, U19.4
SCL19: J77.4, J78.4, J79.4, R134.1, U20.4
SCL20: J81.4, J82.4, J83.4, R141.1, U21.4
SCL21: J85.4, J86.4, J87.4, R148.1, U22.4
SCL22: J89.4, J90.4, J91.4, R155.1, U23.4
SCL23: J93.4, J94.4, J95.4, R162.1, U24.4
SCL24: J97.4, J98.4, J99.4, R169.1, U25.4
SCL25: J101.4, J102.4, J103.4, R176.1, U26.4
SCL26: J105.4, J106.4, J107.4, R183.1, U27.4
SCL27: J109.4, J110.4, J111.4, R190.1, U28.4
SCL28: J113.4, J114.4, J115.4, R197.1, U29.4
SCL29: J117.4, J118.4, J119.4, R204.1, U30.4
SCL30: J121.4, J122.4, J123.4, R211.1, U31.4
SCL31: J125.4, J126.4, J127.4, R218.1, U32.4
SCL32: J129.4, J130.4, J131.4, R225.1, U33.4
SCL33: J133.4, J134.4, J135.4, R232.1, U34.4
SCL34: J137.4, J138.4, J139.4, R239.1, U35.4
SCL35: J141.4, J142.4, J143.4, R246.1, U36.4
SCL36: J145.4, J146.4, J147.4, R253.1, U37.4
SCL37: J149.4, J150.4, J151.4, R260.1, U38.4
SCL38: J153.4, J154.4, J155.4, R267.1, U39.4
SCL39: J157.4, J158.4, J159.4, R274.1, U40.4
SCL40: J161.4, J162.4, J163.4, R281.1, U41.4
SCL41: J165.4, J166.4, J167.4, R288.1, U42.4
SCL42: J169.4, J170.4, J171.4, R295.1, U43.4
SCL43: J173.4, J174.4, J175.4, R302.1, U44.4
SCL44: J177.4, J178.4, J179.4, R309.1, U45.4
SCL45: J181.4, J182.4, J183.4, R316.1, U46.4
SCL46: J185.4, J186.4, J187.4, R323.1, U47.4
SCL47: J189.4, J190.4, J191.4, R330.1, U48.4
SCL48: J193.4, J194.4, J195.4, R337.1, U49.4
SCL49: J197.4, J198.4, J199.4, R344.1, U50.4
SDA: J1.3, J2.3, J3.3, R2.1, U2.5
SDA1: J5.3, J6.3, J7.3, R9.1, U1.5
SDA2: J9.3, J10.3, J11.3, R16.1, U3.5
SDA3: J13.3, J14.3, J15.3, R23.1, U4.5
SDA4: J17.3, J18.3, J19.3, R30.1, U5.5
SDA5: J21.3, J22.3, J23.3, R37.1, U6.5
SDA6: J25.3, J26.3, J27.3, R44.1, U7.5
SDA7: J29.3, J30.3, J31.3, R51.1, U8.5
SDA8: J33.3, J34.3, J35.3, R58.1, U9.5
SDA9: J37.3, J38.3, J39.3, R65.1, U10.5
SDA10: J41.3, J42.3, J43.3, R72.1, U11.5
SDA11: J45.3, J46.3, J47.3, R79.1, U12.5
SDA12: J49.3, J50.3, J51.3, R86.1, U13.5
SDA13: J53.3, J54.3, J55.3, R93.1, U14.5
SDA14: J57.3, J58.3, J59.3, R100.1, U15.5
SDA15: J61.3, J62.3, J63.3, R107.1, U16.5
SDA16: J65.3, J66.3, J67.3, R114.1, U17.5
SDA17: J69.3, J70.3, J71.3, R121.1, U18.5
SDA18: J73.3, J74.3, J75.3, R128.1, U19.5
SDA19: J77.3, J78.3, J79.3, R135.1, U20.5
SDA20: J81.3, J82.3, J83.3, R142.1, U21.5
SDA21: J85.3, J86.3, J87.3, R149.1, U22.5
SDA22: J89.3, J90.3, J91.3, R156.1, U23.5
SDA23: J93.3, J94.3, J95.3, R163.1, U24.5
SDA24: J97.3, J98.3, J99.3, R170.1, U25.5
SDA25: J101.3, J102.3, J103.3, R177.1, U26.5
SDA26: J105.3, J106.3, J107.3, R184.1, U27.5
SDA27: J109.3, J110.3, J111.3, R191.1, U28.5
SDA28: J113.3, J114.3, J115.3, R198.1, U29.5
SDA29: J117.3, J118.3, J119.3, R205.1, U30.5
SDA30: J121.3, J122.3, J123.3, R212.1, U31.5
SDA31: J125.3, J126.3, J127.3, R219.1, U32.5
SDA32: J129.3, J130.3, J131.3, R226.1, U33.5
SDA33: J133.3, J134.3, J135.3, R233.1, U34.5
SDA34: J137.3, J138.3, J139.3, R240.1, U35.5
SDA35: J141.3, J142.3, J143.3, R247.1, U36.5
SDA36: J145.3, J146.3, J147.3, R254.1, U37.5
SDA37: J149.3, J150.3, J151.3, R261.1, U38.5
SDA38: J153.3, J154.3, J155.3, R268.1, U39.5
SDA39: J157.3, J158.3, J159.3, R275.1, U40.5
SDA40: J161.3, J162.3, J163.3, R282.1, U41.5
SDA41: J165.3, J166.3, J167.3, R289.1, U42.5
SDA42: J169.3, J170.3, J171.3, R296.1, U43.5
SDA43: J173.3, J174.3, J175.3, R303.1, U44.5
SDA44: J177.3, J178.3, J179.3, R310.1, U45.5
SDA45: J181.3, J182.3, J183.3, R317.1, U46.5
SDA46: J185.3, J186.3, J187.3, R324.1, U47.5
SDA47: J189.3, J190.3, J191.3, R331.1, U48.5
SDA48: J193.3, J194.3, J195.3, R338.1, U49.5
SDA49: J197.3, J198.3, J199.3, R345.1, U50.5
VBACKUP: C3.1, R6.2, U2.7
VBACKUP1: C7.1, R11.2, U1.7
VBACKUP2: C11.1, R18.2, U3.7
VBACKUP3: C15.1, R25.2, U4.7
VBACKUP4: C19.1, R32.2, U5.7
VBACKUP5: C23.1, R39.2, U6.7
VBACKUP6: C27.1, R46.2, U7.7
VBACKUP7: C31.1, R53.2, U8.7
VBACKUP8: C35.1, R60.2, U9.7
VBACKUP9: C39.1, R67.2, U10.7
VBACKUP10: C43.1, R74.2, U11.7
VBACKUP11: C47.1, R81.2, U12.7
VBACKUP12: C51.1, R88.2, U13.7
VBACKUP13: C55.1, R95.2, U14.7
VBACKUP14: C59.1, R102.2, U15.7
VBACKUP15: C63.1, R109.2, U16.7
VBACKUP16: C67.1, R116.2, U17.7
VBACKUP17: C71.1, R123.2, U18.7
VBACKUP18: C75.1, R130.2, U19.7
VBACKUP19: C79.1, R137.2, U20.7
VBACKUP20: C83.1, R144.2, U21.7
VBACKUP21: C87.1, R151.2, U22.7
VBACKUP22: C91.1, R158.2, U23.7
VBACKUP23: C95.1, R165.2, U24.7
VBACKUP24: C99.1, R172.2, U25.7
VBACKUP25: C103.1, R179.2, U26.7
VBACKUP26: C107.1, R186.2, U27.7
VBACKUP27: C111.1, R193.2, U28.7
VBACKUP28: C115.1, R200.2, U29.7
VBACKUP29: C119.1, R207.2, U30.7
VBACKUP30: C123.1, R214.2, U31.7
VBACKUP31: C127.1, R221.2, U32.7
VBACKUP32: C131.1, R228.2, U33.7
VBACKUP33: C135.1, R235.2, U34.7
VBACKUP34: C139.1, R242.2, U35.7
VBACKUP35: C143.1, R249.2, U36.7
VBACKUP36: C147.1, R256.2, U37.7
VBACKUP37: C151.1, R263.2, U38.7
VBACKUP38: C155.1, R270.2, U39.7
VBACKUP39: C159.1, R277.2, U40.7
VBACKUP40: C163.1, R284.2, U41.7
VBACKUP41: C167.1, R291.2, U42.7
VBACKUP42: C171.1, R298.2, U43.7
VBACKUP43: C175.1, R305.2, U44.7
VBACKUP44: C179.1, R312.2, U45.7
VBACKUP45: C183.1, R319.2, U46.7
VBACKUP46: C187.1, R326.2, U47.7
VBACKUP47: C191.1, R333.2, U48.7
VBACKUP48: C195.1, R340.2, U49.7
VBACKUP49: C199.1, R347.2, U50.7
